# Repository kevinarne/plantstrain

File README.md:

# Overview
I have a bit of an obsession with plants. This repository contains the work I've done to find ways to track one more piece of information about my plants: weight, or at least something proportional to weight. The theory is that I can identify two things from tracking weight over time: the growth of the plant itself and how much water is in the soil.

# Contents
* Schematic Files
* PCB Layout
* Arduino Sketches
  * Peripheral Sketch for ATTiny85
  * Controller Sketch for microcontroller of your choice

# Theory of Operation
The weight PCB features an integrated strain gauge in a Wheatstone Bridge configuration with a microcontroller (ATTiny85) that reads the voltage (using 10-bit ADC) at two points in the Wheatstone Bridge. The differences in those voltages is directly related to the change in resistance of the strain gauge, which in turn is directly related to the extension or compression of the strain gauge. The ATTiny85 acts as an I2C device with address 0x10 and sends both voltage values (as uint16_t's split into two bytes each) upon request.

# To Do
* The current PCB doesn't feature a current-limiting resistor for the Wheatstone Bridge as a whole, so I've bodged one in to my test board. A current limiting resistor pad should be added to the next spin of the board.
* Communication with the strain gauge board needs to be encapsulated in a class, much like in many Adafruit sensor libraries.
* The strain gauge needs testing and may need an ADC with higher resolution to resolve the small differences.
* I don't like the look of the current strain gauge and will likely tweak it to be more evenly spaced in the next board spin.
* It may make sense to use an internet-connected microcontroller (ESP32 or ESP8266) to store weight values in a remote database.

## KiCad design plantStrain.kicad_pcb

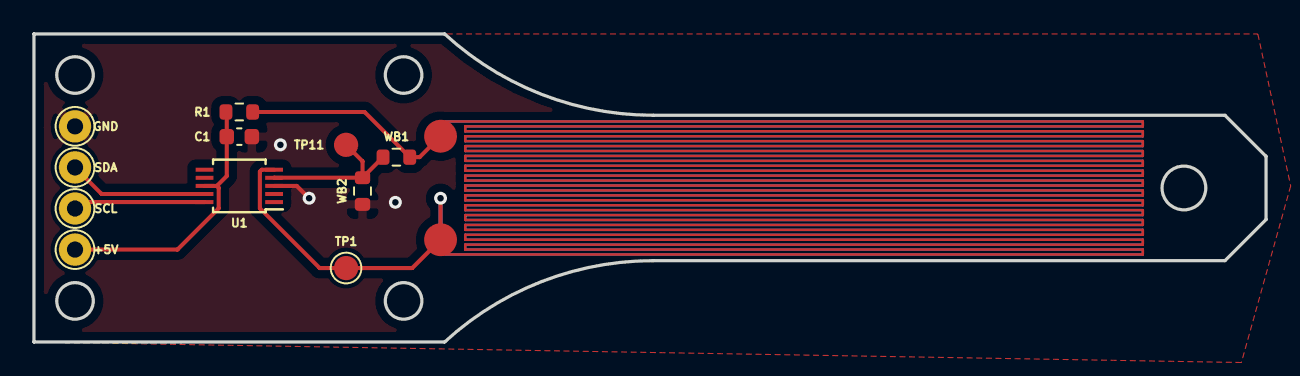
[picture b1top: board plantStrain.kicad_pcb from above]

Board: 2 copper layers, 76.2 x 19.0 mm, 13 parts (1 on the bottom side), 7 nets.

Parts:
C1: CAP; C_0603_1608Metric
R1: 50; R_0603_1608Metric
SG1, SG2: Strain_Gauge; strainLonger
TP1: SG_WB; TestPoint_Pad_D1.5mm
TP7: 5V_I2C; TestPoint_THTPad_D2.0mm_Drill1.0mm
TP8: SDA_I2C; TestPoint_THTPad_D2.0mm_Drill1.0mm
TP9: SCL_I2C; TestPoint_THTPad_D2.0mm_Drill1.0mm
TP10: GND_I2C; TestPoint_THTPad_D2.0mm_Drill1.0mm
TP11: KNOWN_WB; TestPoint_Pad_D1.5mm
U1: ADS1015IDGS; TSSOP-10_3x3mm_P0.5mm
WB1, WB2: R_US; R_0603_1608Metric

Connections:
+5V: C1.1, R1.1, TP7.1, U1.8
GND: C1.2, SG2.2, TP10.1, U1.3, WB2.2
unnamed: R1.2, SG1.1, WB1.1
SCL: TP9.1, U1.10
SDA: TP8.1, U1.9
SG: SG1.2, SG2.1, TP1.1, U1.5
WB_REF: TP11.1, U1.4, WB1.2, WB2.1

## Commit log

2021-05-20 Initial commit with first version of the strain PCB and Arduino code.
2021-05-21 Added README.md to explain what the project is about.
2021-05-22 Changed from Wire library to TinyWireS. Currently the device isn't responding to the controller at all, so more debugging will be needed.
2021-05-30 Modifying the PCB design to a half-bridge with longer strain-sensing units to improve the chance of noticing a change in resistance. Current-limiting resistor also added. In the process of switching 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
2021-06-03 Started updating the board for the strain gauge. Removed unused components and started placing the new ones. Next step is routing.
2021-06-06 Routed new board. Needs some more attention to the silkscreen layers to make it easy to use.
2021-06-22 Second version of PCB sent to fab house.
